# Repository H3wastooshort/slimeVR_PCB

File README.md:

# some kind of SlimeVR project

## Schematic

## PCB

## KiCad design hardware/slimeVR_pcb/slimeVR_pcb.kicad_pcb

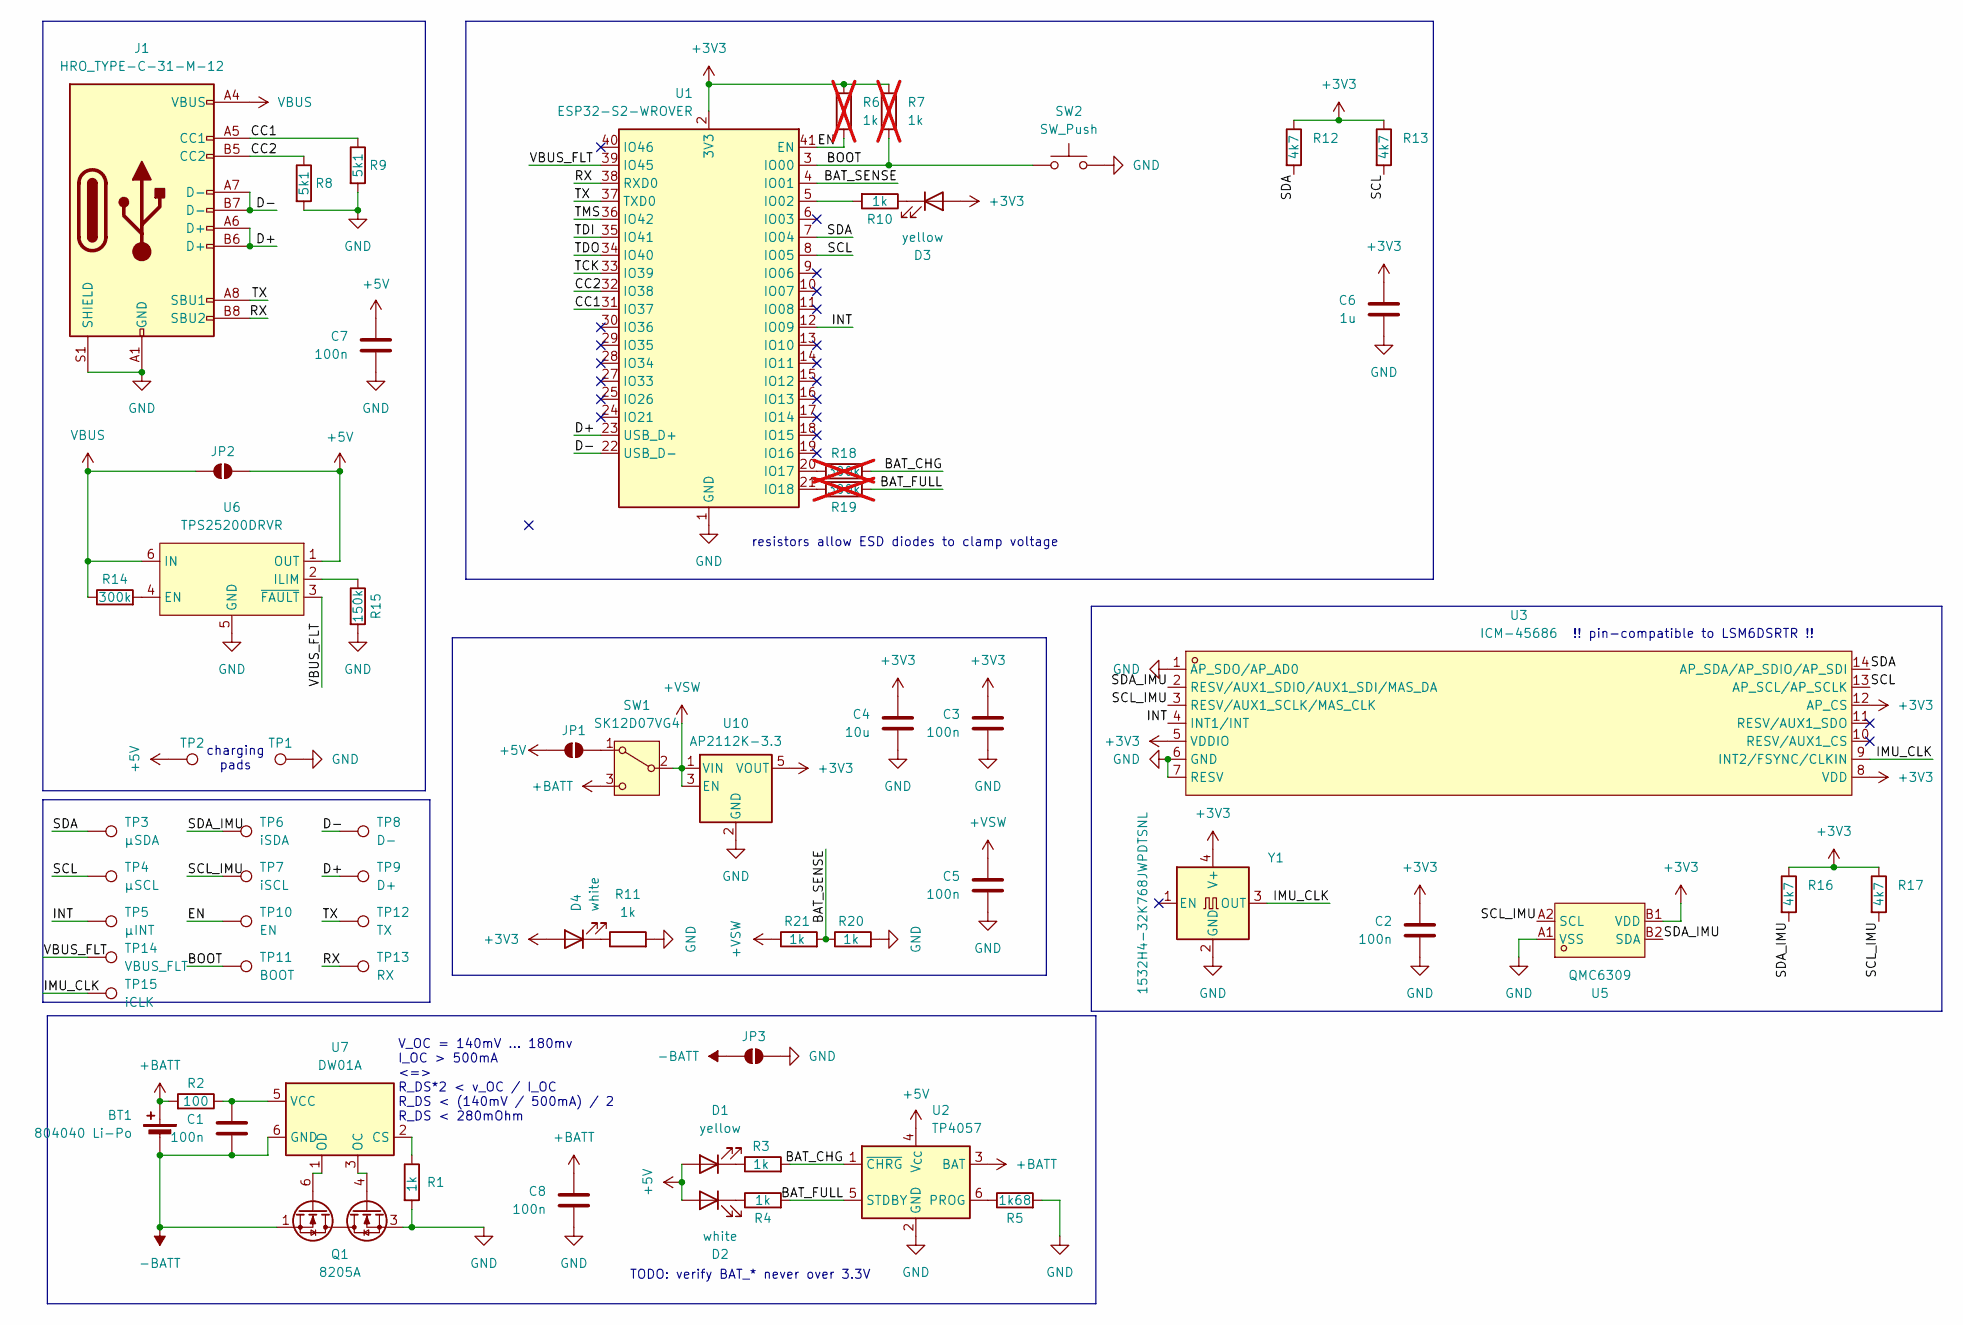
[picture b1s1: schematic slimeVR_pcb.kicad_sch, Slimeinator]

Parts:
BT1: 804040 Li-Po; JST_EH_B2B-EH-A_1x02_P2.50mm_Vertical
C1, C2, C3, C5, C7, C8: 100n; C_0603_1608Metric_Pad1.08x0.95mm_HandSolder; LCSC C14663
C4: 10u; C_0603_1608Metric_Pad1.08x0.95mm_HandSolder; LCSC C19702
C6: 1u; C_0603_1608Metric_Pad1.08x0.95mm_HandSolder; LCSC C15849
D1, D3: yellow; LED_0805_2012Metric_Pad1.15x1.40mm_HandSolder; LCSC C2296
D2, D4: white; LED_0805_2012Metric_Pad1.15x1.40mm_HandSolder; LCSC C34499
J1: HRO_TYPE-C-31-M-12; USB_C_Receptacle_HRO_TYPE-C-31-M-12; LCSC Part C165948
JP1, JP2, JP3: SolderJumper_2_Open; SolderJumper-2_P1.3mm_Open_TrianglePad1.0x1.5mm
Q1: 8205A; SOT-23-6; LCSC Part C2762931
R1, R3, R4, R10, R11, R20, R21: 1k; R_0603_1608Metric_Pad0.98x0.95mm_HandSolder; LCSC C21190
R2: 100; R_0603_1608Metric_Pad0.98x0.95mm_HandSolder; LCSC C22775
R5: 1k68; R_0603_1608Metric_Pad0.98x0.95mm_HandSolder; LCSC C4177
R6, R7: 1k; R_0603_1608Metric_Pad0.98x0.95mm_HandSolder; LCSC C21190; not fitted
R8, R9: 5k1; R_0603_1608Metric_Pad0.98x0.95mm_HandSolder; LCSC C23186
R12, R13, R16, R17: 4k7; R_0603_1608Metric_Pad0.98x0.95mm_HandSolder; LCSC C23162
R14: 300k; R_0603_1608Metric_Pad0.98x0.95mm_HandSolder; LCSC C23024
R15: 150k; R_0603_1608Metric_Pad0.98x0.95mm_HandSolder; LCSC C22807
R18, R19: 300k; R_0603_1608Metric_Pad0.98x0.95mm_HandSolder; LCSC C23024; not fitted
SW1: SK12D07VG4; SW_Slide_SPDT_Angled_CK_OS102011MA1Q; LCSC Part C393937
SW2: SW_Push; SW_Push_1P1T_NO_CK_KSC7xxJ
TP1: GND; TestPoint_Pad_4.0x4.0mm
TP2: +5V; TestPoint_Pad_4.0x4.0mm
TP3: µSDA; TestPoint_Pad_D1.0mm
TP4: µSCL; TestPoint_Pad_D1.0mm
TP5: µINT; TestPoint_Pad_D1.0mm
TP6: iSDA; TestPoint_Pad_D1.0mm
TP7: iSCL; TestPoint_Pad_D1.0mm
TP8: D-; TestPoint_Pad_D1.0mm
TP9: D+; TestPoint_Pad_D1.0mm
TP10: EN; TestPoint_Pad_D1.0mm
TP11: BOOT; TestPoint_Pad_D1.0mm
TP12: TX; TestPoint_Pad_D1.0mm
TP13: RX; TestPoint_Pad_D1.0mm
TP14: VBUS_FLT; TestPoint_Pad_D1.0mm
TP15: iCLK; TestPoint_Pad_D1.0mm
U1: ESP32-S2-WROVER
U2: TP4057; TSOT-23-6; LCSC Part C725791
U3: ICM-45686; LGA-14_L3.0-W2.5-P0.50-TL; LCSC Part C22459454
U5: QMC6309; X1-WLB0808-4_L0.8-W0.8-P0.40-TL; LCSC Part C5439871
U6: TPS25200DRVR; WSON-6-1EP_2x2mm_P0.65mm_EP1x1.6mm; LCSC Part C128401
U7: DW01A; SOT-23-6; LCSC Part C2927799
U10: AP2112K-3.3; SOT-23-5; LCSC Part C51118
Y1: 1532H4-32K768JWPDTSNL; OSC-SMD_4P-L3.2-W2.5-CJ13-320001210A20; LCSC C5383164

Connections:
+3V3: C2.1, C3.1, C4.1, C6.1, D3.2 (A), D4.2 (A), R6.1, R7.1, R12.1, R13.1, R16.1, R17.1, U1.2 (3V3), U3.5 (VDDIO), U3.8 (VDD), U3.12 (AP_CS), U5.B1 (VDD), U10.5 (VOUT), Y1.4 (V+)
+5V: C7.1, D1.2 (A), D2.2 (A), JP1.1 (A), JP2.2 (B), TP2.1, U2.4 (V_{CC}), U6.1 (OUT)
+BATT: BT1.1 (+), C8.1, R2.2, SW1.3 (C), U2.3 (BAT)
+VSW: C5.1, R21.1, SW1.2 (B), U10.1 (VIN), U10.3 (EN)
-BATT: BT1.2 (-), C1.2, JP3.2 (B), Q1.1 (S1), U7.6 (GND)
/BAT_CHG: R3.2, R18.2, U2.1 (~CHRG)
/BAT_FULL: R4.2, R19.2, U2.5 (STDBY)
/BAT_SENSE: R20.1, R21.2, U1.4 (IO01)
/BOOT: R7.2, SW2.2, TP11.1, U1.3 (IO00)
/CC1: J1.A5 (CC1), R9.1, U1.31 (IO37)
/CC2: J1.B5 (CC2), R8.1, U1.32 (IO38)
/D+: J1.A6 (D+), J1.B6 (D+), TP9.1, U1.23 (USB_D+)
/D-: J1.A7 (D-), J1.B7 (D-), TP8.1, U1.22 (USB_D-)
/EN: R6.2, TP10.1, U1.41 (EN)
/IMU_CLK: TP15.1, U3.9 (INT2/FSYNC/CLKIN), Y1.3 (OUT)
/INT: TP5.1, U1.12 (IO09), U3.4 (INT1/INT)
/RX: J1.B8 (SBU2), TP13.1, U1.38 (RXD0)
/SCL: R13.2, TP4.1, U1.8 (IO05), U3.13 (AP_SCL/AP_SCLK)
/SCL_IMU: R17.2, TP7.1, U3.3 (RESV/AUX1_SCLK/MAS_CLK), U5.A2 (SCL)
/SDA: R12.2, TP3.1, U1.7 (IO04), U3.14 (AP_SDA/AP_SDIO/AP_SDI)
/SDA_IMU: R16.2, TP6.1, U3.2 (RESV/AUX1_SDIO/AUX1_SDI/MAS_DA), U5.B2 (SDA)
/TCK: U1.33 (IO39)
/TDI: U1.35 (IO41)
/TDO: U1.34 (IO40)
/TMS: U1.36 (IO42)
/TX: J1.A8 (SBU1), TP12.1, U1.37 (TXD0)
/VBUS_FLT: TP14.1, U1.39 (IO45), U6.3 (~FAULT)
GND: C2.2, C3.2, C4.2, C5.2, C6.2, C7.2, C8.2, J1.A1 (GND), J1.A12 (GND), J1.B1 (GND), J1.B12 (GND), J1.S1 (SHIELD), JP3.1 (A), Q1.3 (S2), R1.2, R5.2, R8.2, R9.2, R11.2, R15.2, R20.2, SW2.1, TP1.1, U1.1 (GND), U1.26 (GND), U1.42 (GND), U1.43 (GND), U2.2 (GND), U3.1 (AP_SDO/AP_AD0), U3.6 (GND), U3.7 (RESV), U5.A1 (VSS), U6.5 (GND), U6.7 (EP), U10.2 (GND), Y1.2 (GND)
unnamed: D1.1 (K), R3.1
unnamed: D2.1 (K), R4.1
unnamed: D3.1 (K), R10.1
unnamed: D4.1 (K), R11.1
unnamed: JP1.2 (B), SW1.1 (A)
unnamed: Q1.6 (G1), U7.1 (OD)
unnamed: Q1.4 (G2), U7.3 (OC)
unnamed: R10.2, U1.5 (IO02)
unnamed: R18.1, U1.20 (IO17)
unnamed: R19.1, U1.21 (IO18)
unnamed: R5.1, U2.6 (PROG)
unnamed: R14.2, U6.4 (EN)
unnamed: R15.1, U6.2 (ILIM)
unnamed: R1.1, U7.2 (CS)
unnamed: C1.1, R2.1, U7.5 (VCC)
VBUS: J1.A4 (VBUS), J1.A9 (VBUS), J1.B4 (VBUS), J1.B9 (VBUS), JP2.1 (A), R14.1, U6.6 (IN)

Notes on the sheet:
!! pin-compatible to LSM6DSRTR !!
V_OC = 140mV ... 180mv I_OC > 500mA <=> R_DS*2 < v_OC / I_OC R_DS < (140mV / 500mA) / 2 R_DS < 280mOhm
TODO: verify BAT_* never over 3.3V
charging pads
resistors allow ESD diodes to clamp voltage

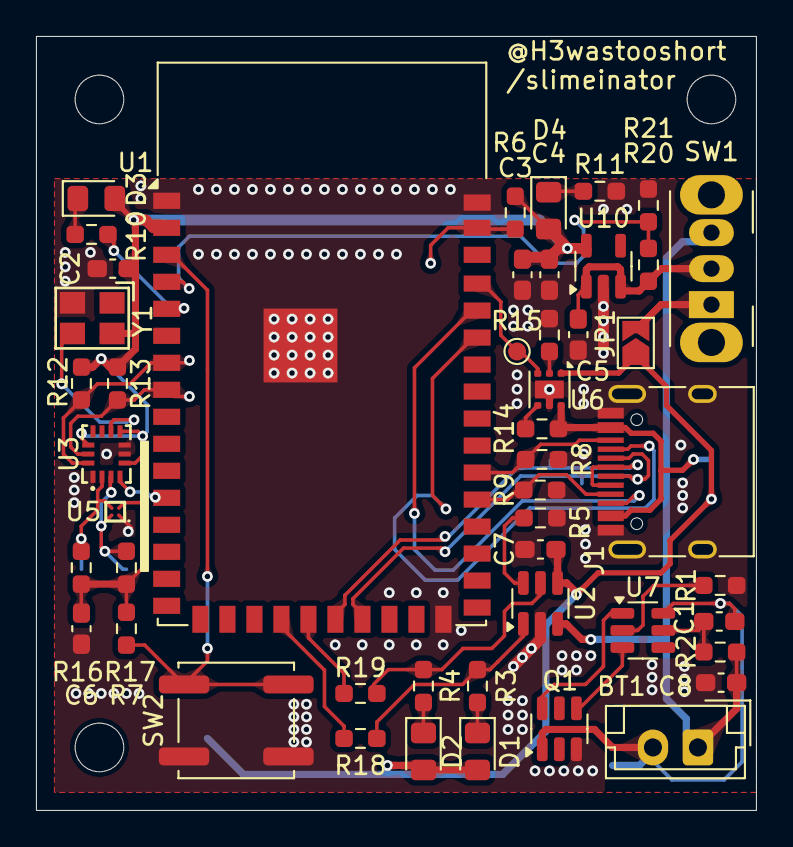
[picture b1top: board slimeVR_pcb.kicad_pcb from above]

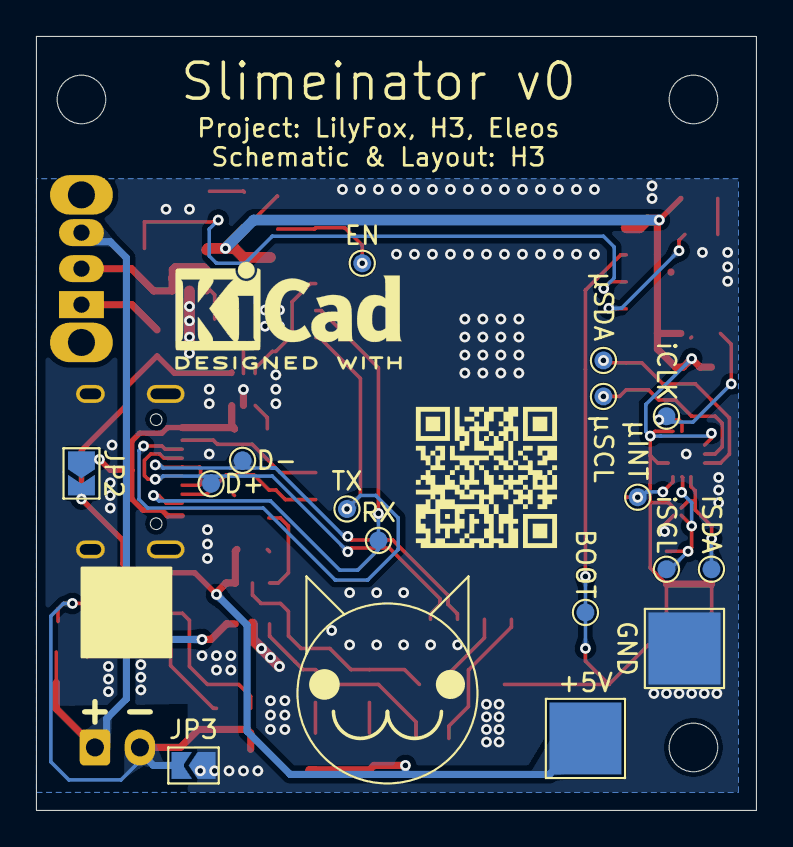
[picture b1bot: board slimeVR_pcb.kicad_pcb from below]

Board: 2 copper layers, 40.0 x 43.0 mm, 65 parts (17 on the bottom side), 40 nets.

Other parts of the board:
CAT**: PCBcat

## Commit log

2025-05-05 switch to esp32s2
2025-07-27 stuff
2025-07-27 continue pcb, cleanup schematic
2025-07-27 add protection circuit
2025-07-27 render PCB
2025-07-27 show renders in readme
2025-07-27 case sensitive urls :grrr:
2025-07-27 cleanup pcb
2025-07-27 routed IMU
2025-07-27 fix DRC, cleanup
2025-07-28 tiredly add testpads
2025-07-28 more testpad
2025-07-28 clearences
2025-07-30 implement garfields suggestions, cleanup board, add TPs
2025-07-30 add decoupleing caps
2025-07-30 cleanup silkscreen, ground unused open-drain
2025-07-30 add solderjumpers for charging signals
2025-07-30 mark unused esp pins
2025-07-31 replace charging signal jumpers with resistors these allow the internal ESD diodes of the ESP32S2 to clamp the valotage to safe levels
2025-07-31 add mounting holes
2025-08-01 cleanup, dw01 calc
2025-08-02 add debugging footprints
2025-08-02 allow reading vbus fault
2025-08-02 gitignore
2025-08-04 partsel round 1
2025-08-04 add 1mm to 3 sides for sliding into rails in case
2025-08-04 partsel round 2
2025-08-04 add silkscreen labels
2025-08-04 adjust readme for repo rename
2025-08-04 fix case-sensitive URL
2025-08-04 add. design rules, pcb cleanup
2025-08-06 allow ESP to read/write CC pins for future use
2025-08-06 tried to use an FUSB302 to supply vconn
2025-08-06 give up on FUSB302 idea i need to supply power via USB C safely, without adding more comonents i need 2 datalines for i2c i could detect shorting of sbu 1 and sbu 2, then use the CC or D+/D- pins for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
2025-08-07 fix typo
2025-08-07 actually fix typo...
2025-08-22 fixup partsel, fixup silkscreen
2025-08-22 decoration
2025-08-22 fixup
2025-08-22 fixup LCSC tags
2025-08-22 add oscillator for IMU
2025-08-22 fix osc footprint
2025-08-22 silk n stuff
2025-08-22 pcb paper size
2025-08-22 add qrcode to repo
